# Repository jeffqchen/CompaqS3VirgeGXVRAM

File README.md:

# VRAM Expansion Board for Compaq S3 Virge GX & Matrox Mystique 220 Video Cards

The Compaq S3 Virge GX video card comes with 2MB of VRAM onboard, and a dual pin header interface for an add-on board to upgrade up to 4MB VRAM in total.

However, this add-on board is difficult to find at a reasonable price nowadays. Hence the need for this project.

Also, I've added additional support for a BIOS chip with a modern pinout scheme, in contrast to the weird one Compaq decided to use on their card. Just in case you are facing a corrupted BIOS situation, you can easily remove the stock one and install your own.

## Extra Compatibility

Later, I've noticed that this expansion board is also completely compatible with the Compaq Matrox Mystique 220, boosting the total VRAM to 4MB.

To learn all the findings I obtained during creating this board, as well as how to build the board, please visit the [Wiki](https://github.com/jeffqchen/CompaqS3VirgeGXVRAM/wiki) pages.

------------
Special Thanks

rain2xx - [Twitter](https://twitter.com/rain2xx)
- for extra photos of a 3rd party VRAM board
------------
Shield: [![CC BY-SA 4.0][cc-by-sa-shield]][cc-by-sa]

This work is licensed under a
[Creative Commons Attribution-ShareAlike 4.0 International License][cc-by-sa].

[![CC BY-SA 4.0][cc-by-sa-image]][cc-by-sa]

[cc-by-sa]: http://creativecommons.org/licenses/by-sa/4.0/
[cc-by-sa-image]: https://licensebuttons.net/l/by-sa/4.0/88x31.png
[cc-by-sa-shield]: https://img.shields.io/badge/License-CC%20BY--SA%204.0-lightgrey.svg

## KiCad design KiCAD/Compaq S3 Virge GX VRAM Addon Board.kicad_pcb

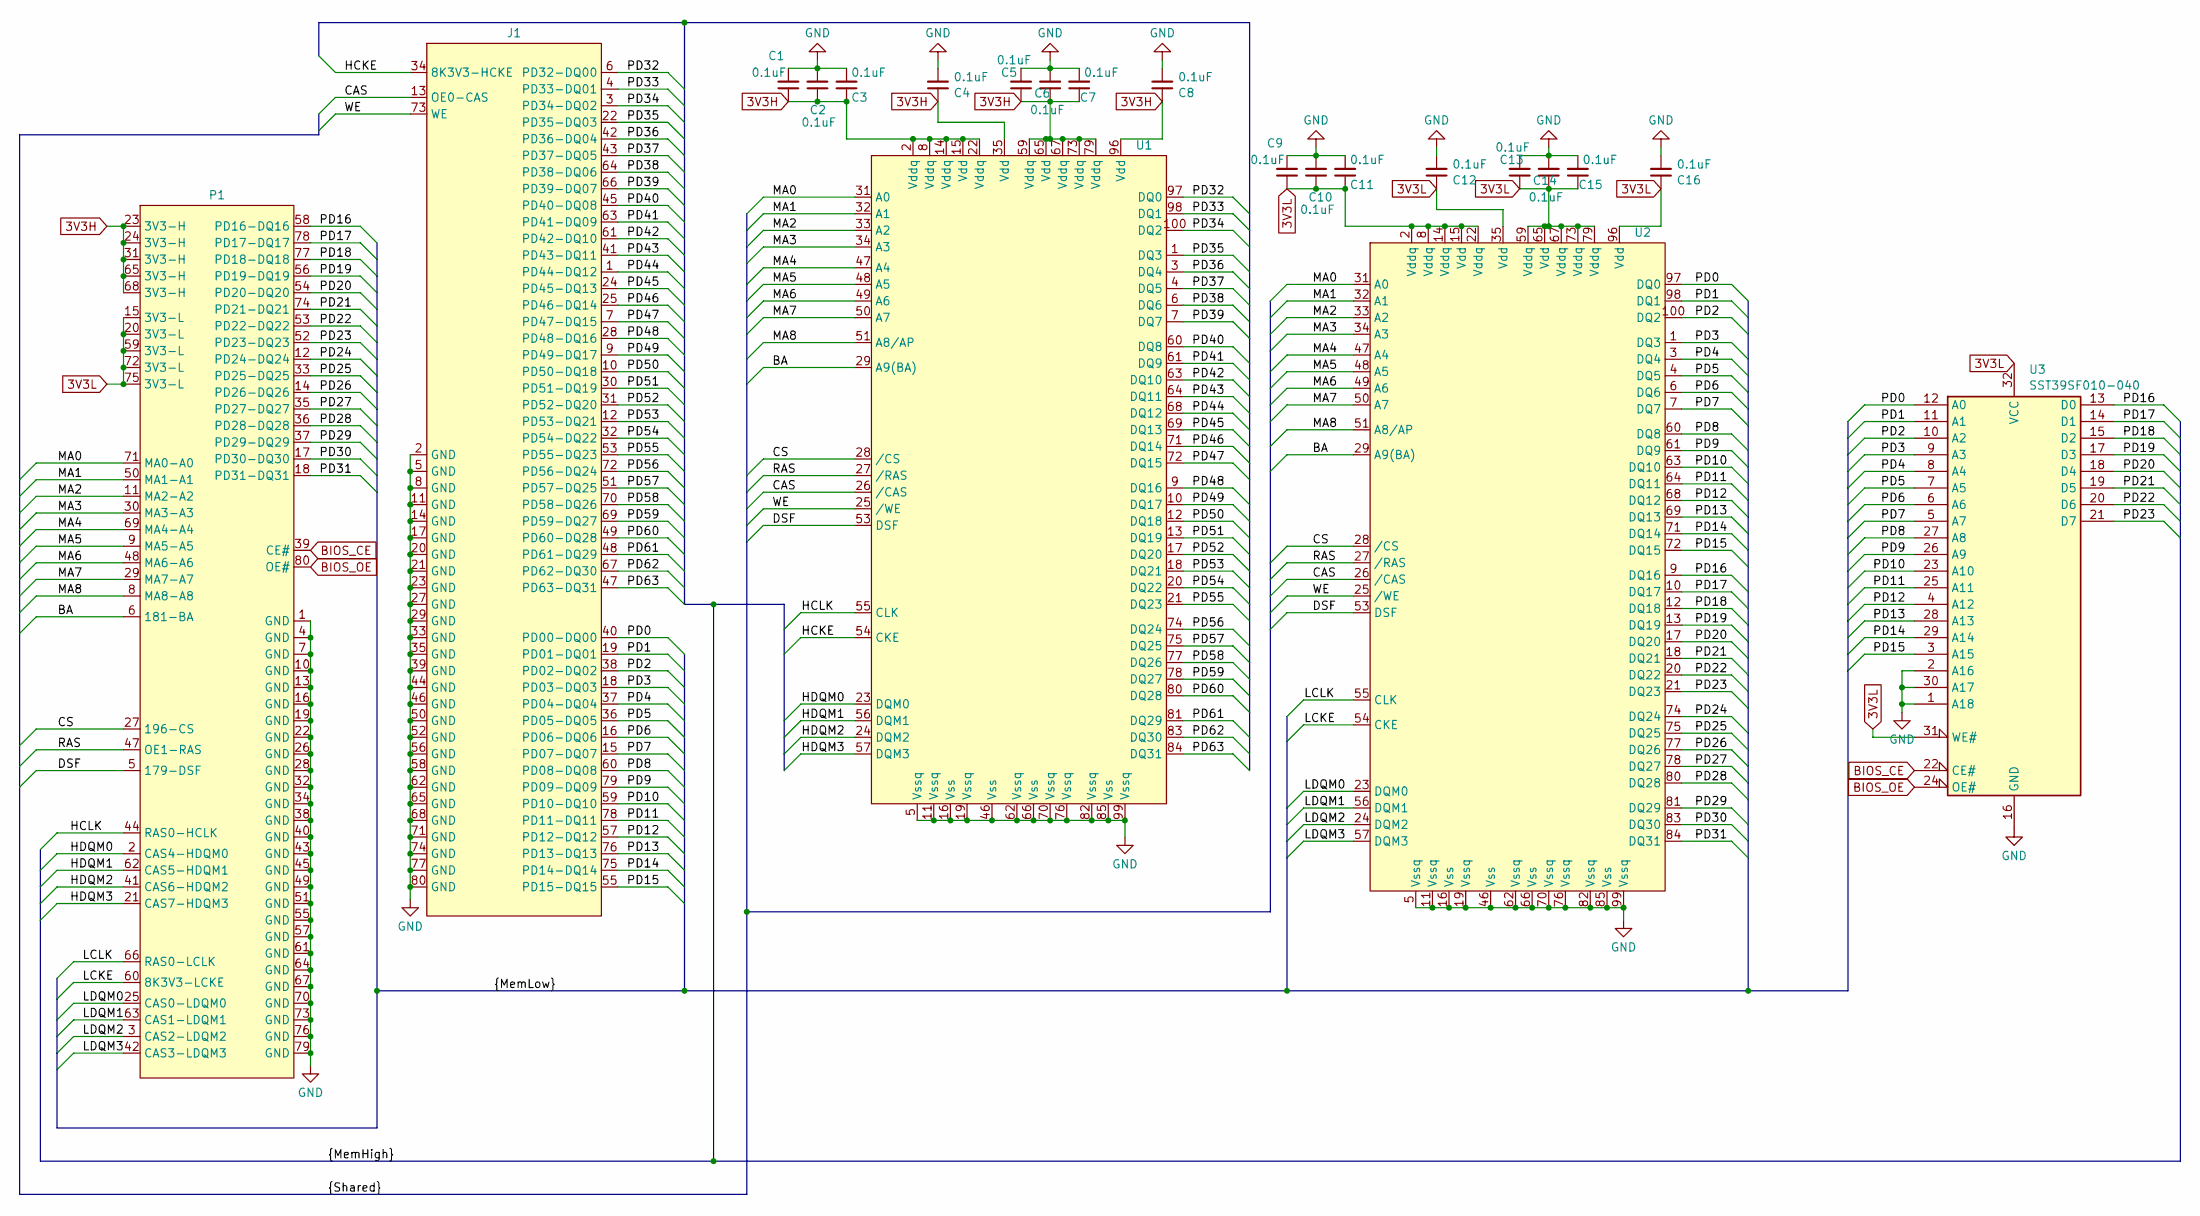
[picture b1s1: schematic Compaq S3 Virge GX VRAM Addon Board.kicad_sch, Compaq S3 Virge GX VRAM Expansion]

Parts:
C1, C2, C3, C4, C5, C6, C7, C8, C9, C10, C11, C12, C13, C14, C15, C16: 0.1uF; C_0603_1608Metric_Pad1.08x0.95mm_HandSolder
J1: Top Pin Header
P1: Bottom Pin Header
U1, U2: PQFP-100_14x20mm_P0.65mm
U3: SST39SF010-040; PLCC-32_THT-Socket

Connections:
3V3H: C1.1, C2.1, C3.1, C4.1, C5.1, C6.1, C7.1, C8.1, P1.23 (3V3-H), P1.24 (3V3-H), P1.31 (3V3-H), P1.65 (3V3-H), P1.68 (3V3-H), U1.2 (Vddq), U1.8 (Vddq), U1.14 (Vddq), U1.15 (Vdd), U1.22 (Vddq), U1.35 (Vdd), U1.59 (Vddq), U1.65 (Vdd), U1.67 (Vddq), U1.73 (Vddq), U1.79 (Vddq), U1.96 (Vdd)
3V3L: C9.1, C10.1, C11.1, C12.1, C13.1, C14.1, C15.1, C16.1, P1.15 (3V3-L), P1.20 (3V3-L), P1.59 (3V3-L), P1.72 (3V3-L), P1.75 (3V3-L), U2.2 (Vddq), U2.8 (Vddq), U2.14 (Vddq), U2.15 (Vdd), U2.22 (Vddq), U2.35 (Vdd), U2.59 (Vddq), U2.65 (Vdd), U2.67 (Vddq), U2.73 (Vddq), U2.79 (Vddq), U2.96 (Vdd), U3.31 (WE#), U3.32 (VCC)
/BA: P1.6 (181-BA), U1.29 (A9(BA)), U2.29 (A9(BA))
/CAS: J1.13 (OE0-CAS), U1.26 (/CAS), U2.26 (/CAS)
/CS: P1.27 (196-CS), U1.28 (/CS), U2.28 (/CS)
/DSF: P1.5 (179-DSF), U1.53 (DSF), U2.53 (DSF)
/HCKE: J1.34 (8K3V3-HCKE), U1.54 (CKE)
/HCLK: P1.44 (RAS0-HCLK), U1.55 (CLK)
/HDQM0: P1.2 (CAS4-HDQM0), U1.23 (DQM0)
/HDQM1: P1.62 (CAS5-HDQM1), U1.56 (DQM1)
/HDQM2: P1.41 (CAS6-HDQM2), U1.24 (DQM2)
/HDQM3: P1.21 (CAS7-HDQM3), U1.57 (DQM3)
/LCKE: P1.60 (8K3V3-LCKE), U2.54 (CKE)
/LCLK: P1.66 (RAS0-LCLK), U2.55 (CLK)
/LDQM0: P1.25 (CAS0-LDQM0), U2.23 (DQM0)
/LDQM1: P1.63 (CAS1-LDQM1), U2.56 (DQM1)
/LDQM2: P1.3 (CAS2-LDQM2), U2.24 (DQM2)
/LDQM3: P1.42 (CAS3-LDQM3), U2.57 (DQM3)
/MA0: P1.71 (MA0-A0), U1.31 (A0), U2.31 (A0)
/MA1: P1.50 (MA1-A1), U1.32 (A1), U2.32 (A1)
/MA2: P1.11 (MA2-A2), U1.33 (A2), U2.33 (A2)
/MA3: P1.30 (MA3-A3), U1.34 (A3), U2.34 (A3)
/MA4: P1.69 (MA4-A4), U1.47 (A4), U2.47 (A4)
/MA5: P1.9 (MA5-A5), U1.48 (A5), U2.48 (A5)
/MA6: P1.48 (MA6-A6), U1.49 (A6), U2.49 (A6)
/MA7: P1.29 (MA7-A7), U1.50 (A7), U2.50 (A7)
/MA8: P1.8 (MA8-A8), U1.51 (A8/AP), U2.51 (A8/AP)
/PD0: J1.40 (PD00-DQ00), U2.97 (DQ0), U3.12 (A0)
/PD1: J1.19 (PD01-DQ01), U2.98 (DQ1), U3.11 (A1)
/PD2: J1.38 (PD02-DQ02), U2.100 (DQ2), U3.10 (A2)
/PD3: J1.18 (PD03-DQ03), U2.1 (DQ3), U3.9 (A3)
/PD4: J1.37 (PD04-DQ04), U2.3 (DQ4), U3.8 (A4)
/PD5: J1.36 (PD05-DQ05), U2.4 (DQ5), U3.7 (A5)
/PD6: J1.16 (PD06-DQ06), U2.6 (DQ6), U3.6 (A6)
/PD7: J1.15 (PD07-DQ07), U2.7 (DQ7), U3.5 (A7)
/PD8: J1.60 (PD08-DQ08), U2.60 (DQ8), U3.27 (A8)
/PD9: J1.79 (PD09-DQ09), U2.61 (DQ9), U3.26 (A9)
/PD10: J1.59 (PD10-DQ10), U2.63 (DQ10), U3.23 (A10)
/PD11: J1.78 (PD11-DQ11), U2.64 (DQ11), U3.25 (A11)
/PD12: J1.57 (PD12-DQ12), U2.68 (DQ12), U3.4 (A12)
/PD13: J1.76 (PD13-DQ13), U2.69 (DQ13), U3.28 (A13)
/PD14: J1.75 (PD14-DQ14), U2.71 (DQ14), U3.29 (A14)
/PD15: J1.55 (PD15-DQ15), U2.72 (DQ15), U3.3 (A15)
/PD16: P1.58 (PD16-DQ16), U2.9 (DQ16), U3.13 (D0)
/PD17: P1.78 (PD17-DQ17), U2.10 (DQ17), U3.14 (D1)
/PD18: P1.77 (PD18-DQ18), U2.12 (DQ18), U3.15 (D2)
/PD19: P1.56 (PD19-DQ19), U2.13 (DQ19), U3.17 (D3)
/PD20: P1.54 (PD20-DQ20), U2.17 (DQ20), U3.18 (D4)
/PD21: P1.74 (PD21-DQ21), U2.18 (DQ21), U3.19 (D5)
/PD22: P1.53 (PD22-DQ22), U2.20 (DQ22), U3.20 (D6)
/PD23: P1.52 (PD23-DQ23), U2.21 (DQ23), U3.21 (D7)
/PD24: P1.12 (PD24-DQ24), U2.74 (DQ24)
/PD25: P1.33 (PD25-DQ25), U2.75 (DQ25)
/PD26: P1.14 (PD26-DQ26), U2.77 (DQ26)
/PD27: P1.35 (PD27-DQ27), U2.78 (DQ27)
/PD28: P1.36 (PD28-DQ28), U2.80 (DQ28)
/PD29: P1.37 (PD29-DQ29), U2.81 (DQ29)
/PD30: P1.17 (PD30-DQ30), U2.83 (DQ30)
/PD31: P1.18 (PD31-DQ31), U2.84 (DQ31)
/PD32: J1.6 (PD32-DQ00), U1.97 (DQ0)
/PD33: J1.4 (PD33-DQ01), U1.98 (DQ1)
/PD34: J1.3 (PD34-DQ02), U1.100 (DQ2)
/PD35: J1.22 (PD35-DQ03), U1.1 (DQ3)
/PD36: J1.42 (PD36-DQ04), U1.3 (DQ4)
/PD37: J1.43 (PD37-DQ05), U1.4 (DQ5)
/PD38: J1.64 (PD38-DQ06), U1.6 (DQ6)
/PD39: J1.66 (PD39-DQ07), U1.7 (DQ7)
/PD40: J1.45 (PD40-DQ08), U1.60 (DQ8)
/PD41: J1.63 (PD41-DQ09), U1.61 (DQ9)
/PD42: J1.61 (PD42-DQ10), U1.63 (DQ10)
/PD43: J1.41 (PD43-DQ11), U1.64 (DQ11)
/PD44: J1.1 (PD44-DQ12), U1.68 (DQ12)
/PD45: J1.24 (PD45-DQ13), U1.69 (DQ13)
/PD46: J1.25 (PD46-DQ14), U1.71 (DQ14)
/PD47: J1.7 (PD47-DQ15), U1.72 (DQ15)
/PD48: J1.28 (PD48-DQ16), U1.9 (DQ16)
/PD49: J1.9 (PD49-DQ17), U1.10 (DQ17)
/PD50: J1.10 (PD50-DQ18), U1.12 (DQ18)
/PD51: J1.30 (PD51-DQ19), U1.13 (DQ19)
/PD52: J1.31 (PD52-DQ20), U1.17 (DQ20)
/PD53: J1.12 (PD53-DQ21), U1.18 (DQ21)
/PD54: J1.32 (PD54-DQ22), U1.20 (DQ22)
/PD55: J1.53 (PD55-DQ23), U1.21 (DQ23)
/PD56: J1.72 (PD56-DQ24), U1.74 (DQ24)
/PD57: J1.51 (PD57-DQ25), U1.75 (DQ25)
/PD58: J1.70 (PD58-DQ26), U1.77 (DQ26)
/PD59: J1.69 (PD59-DQ27), U1.78 (DQ27)
/PD60: J1.49 (PD60-DQ28), U1.80 (DQ28)
/PD61: J1.48 (PD61-DQ29), U1.81 (DQ29)
/PD62: J1.67 (PD62-DQ30), U1.83 (DQ30)
/PD63: J1.47 (PD63-DQ31), U1.84 (DQ31)
/RAS: P1.47 (OE1-RAS), U1.27 (/RAS), U2.27 (/RAS)
/WE: J1.73 (WE), U1.25 (/WE), U2.25 (/WE)
BIOS_CE: P1.39 (CE#), U3.22 (CE#)
BIOS_OE: P1.80 (OE#), U3.24 (OE#)
GND: C1.2, C2.2, C3.2, C4.2, C5.2, C6.2, C7.2, C8.2, C9.2, C10.2, C11.2, C12.2, C13.2, C14.2, C15.2, C16.2, J1.2 (GND), J1.5 (GND), J1.8 (GND), J1.11 (GND), J1.14 (GND), J1.17 (GND), J1.20 (GND), J1.21 (GND), J1.23 (GND), J1.27 (GND), J1.29 (GND), J1.33 (GND), J1.35 (GND), J1.39 (GND), J1.44 (GND), J1.46 (GND), J1.50 (GND), J1.52 (GND), J1.56 (GND), J1.58 (GND), J1.62 (GND), J1.65 (GND), J1.68 (GND), J1.71 (GND), J1.74 (GND), J1.77 (GND), J1.80 (GND), P1.1 (GND), P1.4 (GND), P1.7 (GND), P1.10 (GND), P1.13 (GND), P1.16 (GND), P1.19 (GND), P1.22 (GND), P1.26 (GND), P1.28 (GND), P1.32 (GND), P1.34 (GND), P1.38 (GND), P1.40 (GND), P1.43 (GND), P1.45 (GND), P1.49 (GND), P1.51 (GND), P1.55 (GND), P1.57 (GND), P1.61 (GND), P1.64 (GND), P1.67 (GND), P1.70 (GND), P1.73 (GND), P1.76 (GND), P1.79 (GND), U1.5 (Vssq), U1.11 (Vssq), U1.16 (Vss), U1.19 (Vssq), U1.46 (Vss), U1.62 (Vssq), U1.66 (Vss), U1.70 (Vssq), U1.76 (Vssq), U1.82 (Vssq), U1.85 (Vss), U1.99 (Vssq), U2.5 (Vssq), U2.11 (Vssq), U2.16 (Vss), U2.19 (Vssq), U2.46 (Vss), U2.62 (Vssq), U2.66 (Vss), U2.70 (Vssq), U2.76 (Vssq), U2.82 (Vssq), U2.85 (Vss), U2.99 (Vssq), U3.1 (A18), U3.2 (A16), U3.16 (GND), U3.30 (A17)

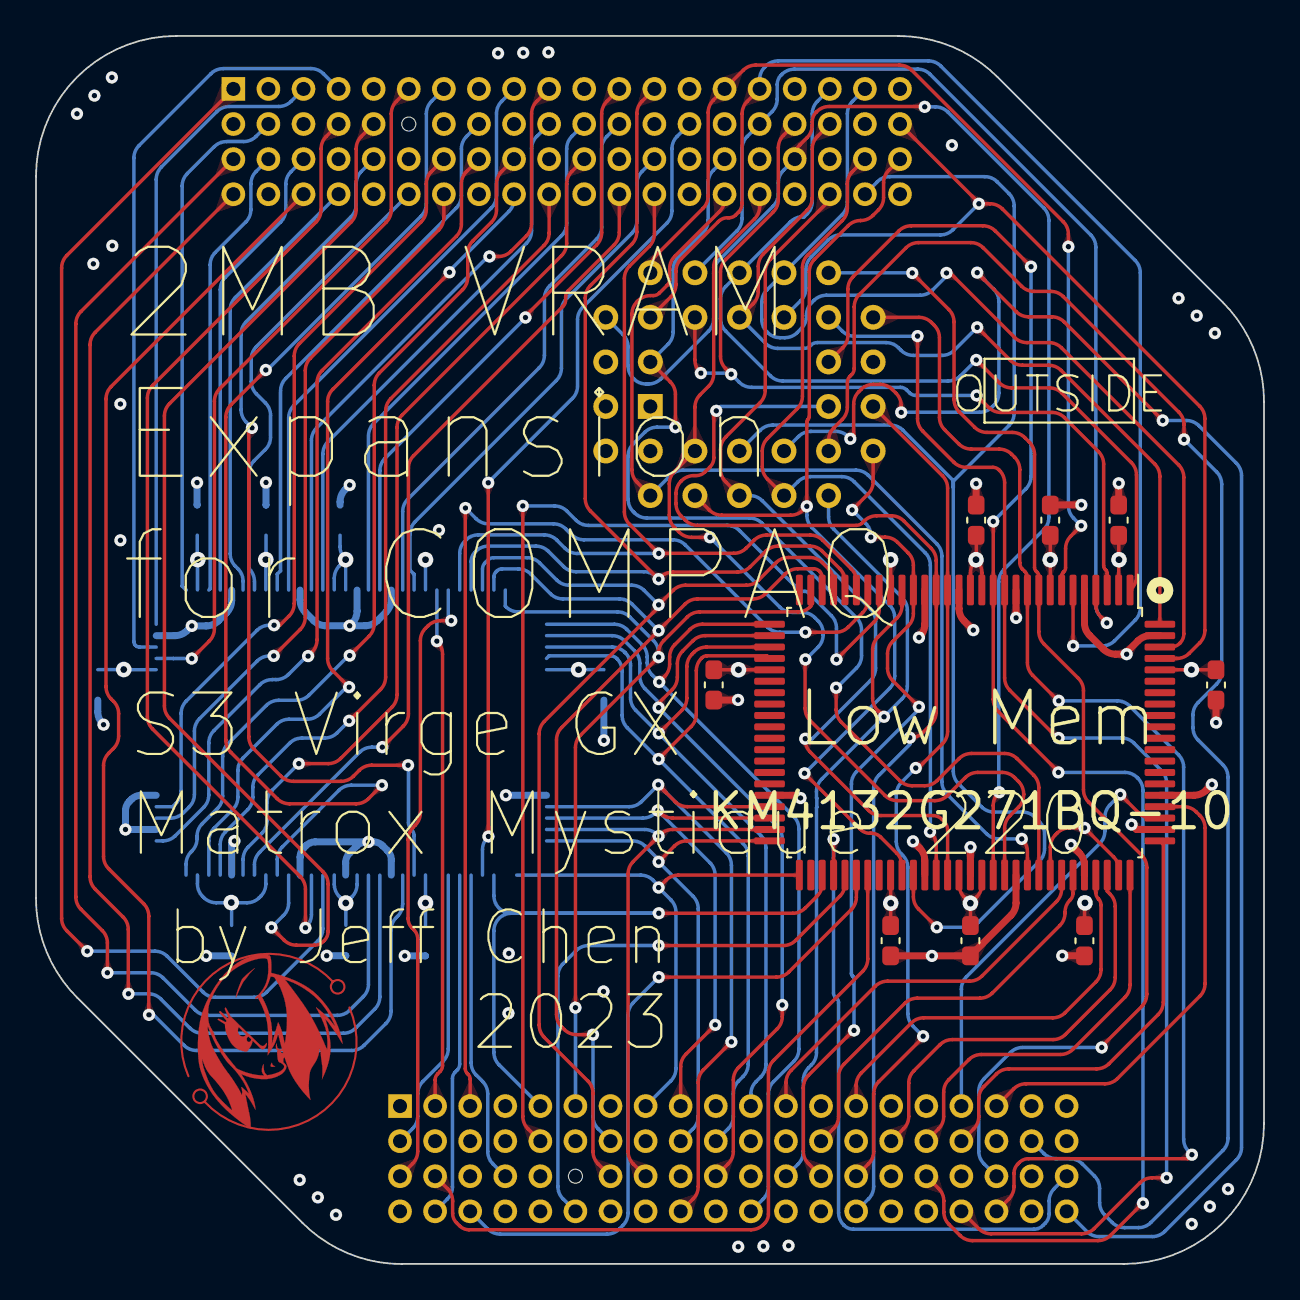
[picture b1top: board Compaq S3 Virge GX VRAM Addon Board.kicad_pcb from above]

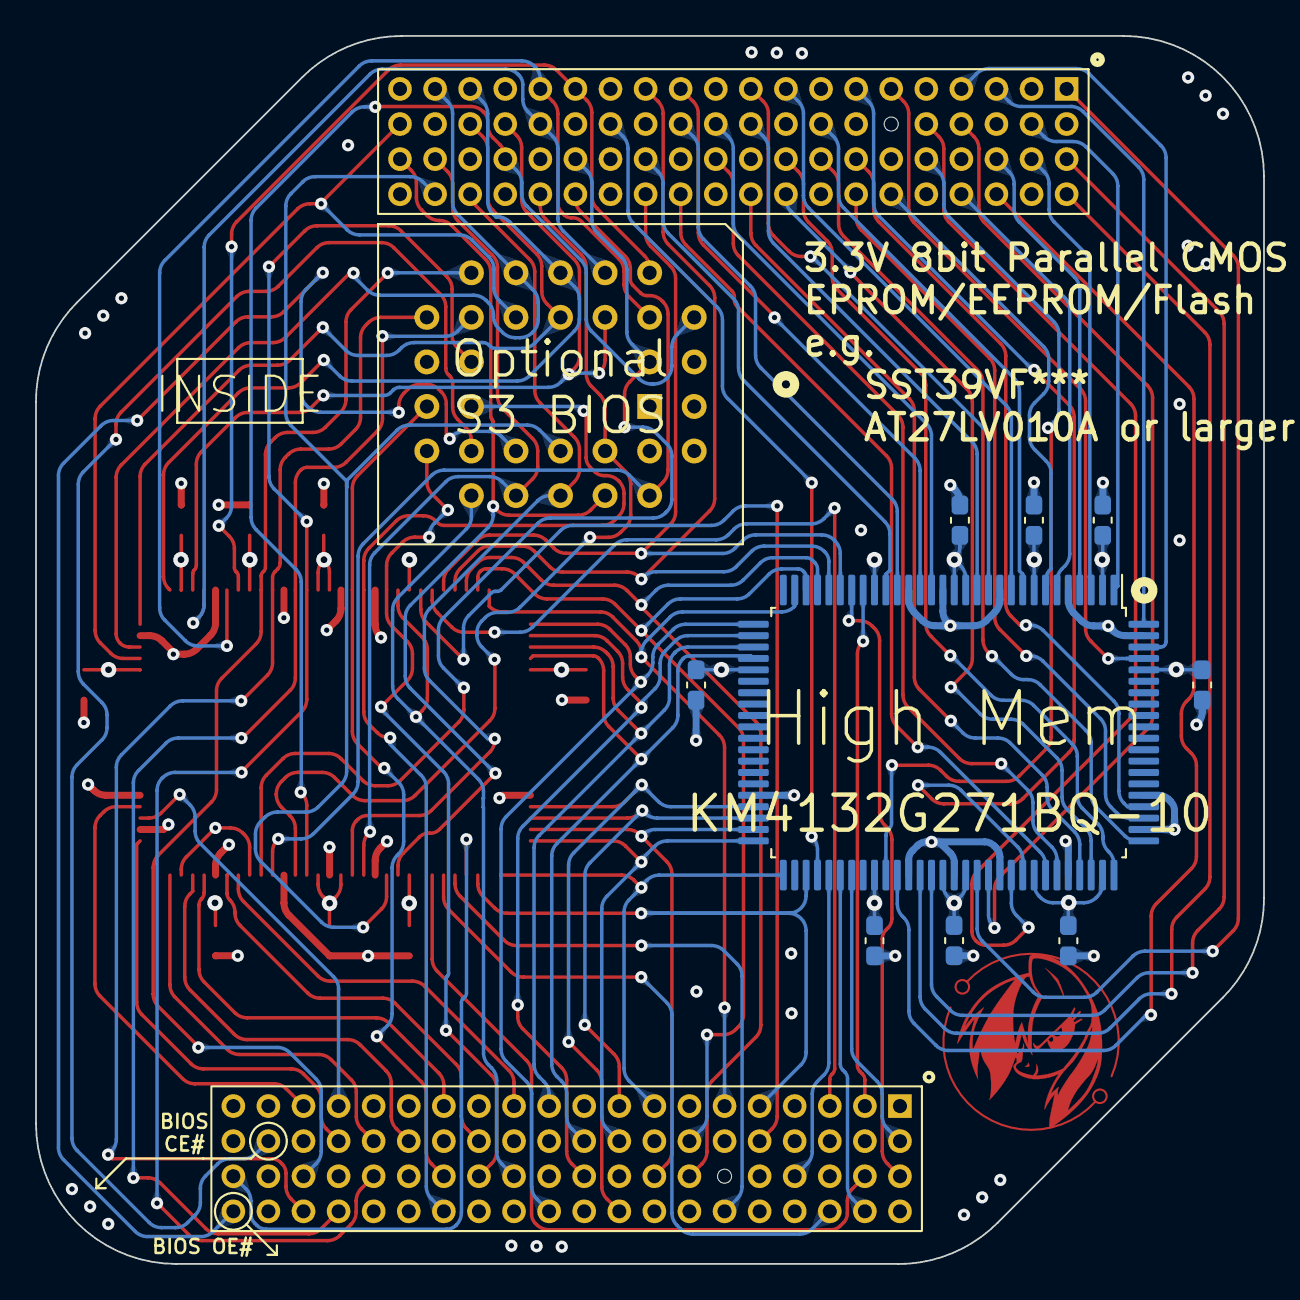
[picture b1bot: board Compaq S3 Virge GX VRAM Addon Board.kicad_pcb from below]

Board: 4 copper layers, 70.0 x 70.0 mm, 21 parts (10 on the bottom side), 96 nets.

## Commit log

2023-08-17 Create test
2023-08-17 Add KiCAD files
2023-08-17 Add BIOS dumps
    Orignal and Gainward BIOS images.
2023-08-18 Add CCSA license
2023-08-18 Rename LICENSE-CC-BY-SA.txt to LICENSE
2024-01-09 Update PCB project
    Add Mystique 220 compatibility
